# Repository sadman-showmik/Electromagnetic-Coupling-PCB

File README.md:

# Electromagnetic Coupling Link — Resonant Inductive Power Transfer

A KiCad 8 project for a **wireless power link**: a 12 V transmitter drives a tuned coil at ~75 kHz, and a galvanically isolated receiver coil picks up the field, rectifies it and regulates it to **5 V**. It uses only common through-hole parts (NE555, IR2302, IRFZ44N, LM7805).

> Full-page schematic: [`EM_Coupling/EM_Coupling.pdf`](EM_Coupling/EM_Coupling.pdf)

---

## Contents

- [How it works](#how-it-works)
- [Key design values](#key-design-values)
- [Bill of materials](#bill-of-materials)
- [Coils](#coils)
- [Expected performance](#expected-performance)
- [Repository layout](#repository-layout)
- [Opening the project](#opening-the-project)
- [Regenerating the files](#regenerating-the-files)
- [Verification](#verification)
- [Safety notes](#safety-notes)
- [Project status](#project-status)

---

## How it works

```mermaid
flowchart LR
    subgraph TX["Transmitter — 12 V side"]
        A["J1 12 V in<br/>S1 switch"] --> B["U1 NE555<br/>~75 kHz oscillator"]
        B --> C["IC1 IR2302<br/>half-bridge driver"]
        C --> D["Q1 / Q2 IRFZ44N<br/>half-bridge"]
        D --> E["C5 + TX coil<br/>series resonant tank"]
    end
    E -. "magnetic field<br/>(no wires)" .-> F
    subgraph RX["Receiver — isolated side"]
        F["RX coil + C7<br/>resonant pickup"] --> G["D3 / D4<br/>voltage doubler → C6"]
        G --> H["IC2 LM7805<br/>5 V regulator"]
        H --> I["J4 5 V out"]
        G --> J["J5 raw DC out"]
    end
```

### Transmitter (12 V)

| Stage | Parts | What it does |
|---|---|---|
| Power input | J1, S1, C8, C1 | 12 V DC in, on/off switch, input and high-frequency decoupling |
| Oscillator | U1, R1, R4, C11, C10, C2 | NE555 astable, ~75 kHz square wave, ~53 % duty |
| Gate driver | IC1, R2, C4, D2, C3 | IR2302 drives the half-bridge with built-in dead time; D2/C3 bootstrap the high-side gate |
| Power stage | Q1, Q2, R3 | IRFZ44N half-bridge switches the `SW` node between 12 V and GND |
| Resonant tank | C5, TX coil (J2) | Series LC tuned to 75 kHz — a large AC current flows in the coil and makes a strong alternating magnetic field |

### Receiver (isolated)

| Stage | Parts | What it does |
|---|---|---|
| Pickup | RX coil (J3), C7 | Coil tuned to the same 75 kHz so it captures as much energy as possible |
| Rectifier | D3, D4, C6 | Greinacher voltage doubler: about 2× the coil peak voltage as DC (`VRAW`, also on J5) |
| Regulator | IC2, C9 | LM7805 gives a steady 5 V on J4 |
| Protection | D5, D1 | D5 protects the 7805 when C6 discharges first; D1 (5.6 V zener) clamps output over-voltage |

The TX ground (`GND`) and RX ground (`GND_RX`) are **not connected**. Energy crosses only through the magnetic coupling between the two coils.

---

## Key design values

| Quantity | Formula | Value |
|---|---|---|
| Oscillator frequency | f = 1.44 / ((R1 + 2·R4) · C11) | 1.44 / ((1 k + 18.18 k) · 1 nF) ≈ **75 kHz** |
| Duty cycle | (R1 + R4) / (R1 + 2·R4) | ≈ **53 %** |
| Coil inductance for resonance | L = 1 / ((2π f)² · C) with C5 = C7 = 0.1 µF | ≈ **45 µH** per coil |
| Minimum `VRAW` for regulation | 5 V + LM7805 dropout | ≈ **7.5 V** |

---

## Bill of materials

| Reference | Value | Footprint | Qty | Notes |
|---|---|---|---|---|
| C1, C2, C3, C4, C5, C7, C9 | 0.1 µF | `Capacitor_THT:CP_Radial_Tantal_D6.0mm_P5.00mm` | 7 | **C5 and C7: use film, ≥ 250 V** (see notes below) |
| C6 | 470 µF | `Capacitor_THT:CP_Radial_Tantal_D7.0mm_P5.00mm` | 1 | Reservoir, ≥ 25 V |
| C8 | 0.33 µF | `Capacitor_THT:CP_Radial_Tantal_D7.0mm_P5.00mm` | 1 | 12 V input bypass |
| C10 | 10 nF | `Capacitor_THT:CP_Radial_Tantal_D6.0mm_P5.00mm` | 1 | 555 CV filter |
| C11 | 1 nF | `Capacitor_THT:CP_Radial_Tantal_D6.0mm_P5.00mm` | 1 | 555 timing (C0G/film recommended) |
| D1 | 1N5919BG | `3D_Models:DIOAD1405W86L465D235` | 1 | 5.6 V / 3 W zener |
| D2, D3, D4, D5 | 1N4148 | `3D_Models:DIOAD1068W53L380D172` | 4 | |
| IC1 | IR2302SPBF | `3D_Models:SOIC127P600X175-8N` | 1 | Half-bridge driver |
| IC2 | LM7805CT | `3D_Models:TO254P470X1028X1955-3P` | 1 | 5 V regulator |
| J1–J5 | 282843-2 (TE) | `3D_Models:SHDR2W130P0X1016_1X2_1524X900X1550P` | 5 | 12 V in, TX coil, RX coil, 5 V out, raw DC out |
| Q1, Q2 | IRFZ44NPBF | `3D_Models:TO254P483X1016X1994-3P` | 2 | N-MOSFET, TO-220 |
| R1 | 1 kΩ | `Resistor_THT:R_Axial_DIN0204_L3.6mm_D1.6mm_P7.62mm_Horizontal` | 1 | 555 R_A |
| R2 | 100 Ω | same | 1 | Driver input |
| R3 | 10 Ω | same | 1 | Q1 gate |
| R4 | 9.09 kΩ | same | 1 | 555 R_B |
| S1 | EG1218 | `3D_Models:EG1218` | 1 | SPDT slide switch |
| U1 | NE555P | `Package_DIP:DIP-8_W7.62mm` | 1 | Timer |

**Not in the BOM:** the two coils, about 45 µH each (see [Coils](#coils)).

> **Capacitor notes.** The BOM footprints for all capacitors are radial tantalum. That's fine for the DC parts, but **C5 and C7 carry the resonant AC current**, and the voltage across them can exceed 100 V at resonance. Fit polypropylene film capacitors rated **≥ 250 V** there; the 5 mm-pitch footprint fits most 0.1 µF film parts. The KiCad symbol for Q1/Q2 is `IRF540N` (same G-D-S TO-220 pinout), with its value set to IRFZ44NPBF.

A machine-readable BOM is in [`EM_Coupling/EM_Coupling_BOM.csv`](EM_Coupling/EM_Coupling_BOM.csv).

---

## Coils

Both coils are the same design, about **45 µH**, so they resonate at 75 kHz with 0.1 µF.

- Starting point: about **15 turns of 0.8–1.0 mm enamelled copper wire** (or Litz wire) on a **60 mm** diameter former, flat or short solenoid.
- Measure with an LCR meter and adjust turns. If your coil differs, retune: C = 1 / ((2π · 75 kHz)² · L).
- Fine-tune by trimming C5/C7, or adjust R4 to move the oscillator onto the tank's actual resonance.

---

## Expected performance

These are design estimates, not measured results.

| Parameter | Estimate |
|---|---|
| Operating frequency | ~75 kHz |
| Coupling distance | ~1–5 cm (60 mm coils, coaxial) |
| Output | 5 V regulated, roughly 0.3–0.5 W |
| Output current limit | ~100 mA (set by the 1N4148 rectifiers) |

For more output power, replace D3/D4 with faster, higher-current diodes (e.g. UF4001 or 1N5819 Schottky) and raise C6's voltage rating to suit.

---

## Repository layout

```
.
├── README.md
├── docs/
│   └── schematic.svg            # schematic image used in this README
├── EM_Coupling/                 # KiCad 8 project
│   ├── EM_Coupling.kicad_pro
│   ├── EM_Coupling.kicad_sch    # fully wired schematic
│   ├── EM_Coupling.kicad_pcb    # starter PCB: footprints and nets, not routed yet
│   ├── EM_Coupling.pdf          # printable schematic
│   ├── EM_Coupling.net          # exported netlist
│   ├── EM_Coupling_BOM.csv      # exported BOM
│   ├── erc.rpt                  # latest ERC report
│   ├── fp-lib-table             # project footprint library table
│   ├── 3D_Models.pretty/        # project-local SamacSys footprints
│   └── 3D_Models.3dshapes/      # matching STEP models
├── gen_wired.py                 # generates the wired schematic (main generator)
├── gen_schematic.py             # older label-based generator (kept as netlist reference)
├── labels_reference.net         # reference netlist used to check the wired schematic
├── kicad_lib.py                 # helper: reads KiCad symbol libraries
└── build_pcb.py                 # builds the starter PCB using KiCad's pcbnew Python
```

---

## Opening the project

1. Install **KiCad 8.0** or newer.
2. Open `EM_Coupling/EM_Coupling.kicad_pro`.
3. The project ships its own footprint library table (`fp-lib-table`). The nickname `3D_Models` resolves to `EM_Coupling/3D_Models.pretty`, so no global library setup is needed.

---

## Regenerating the files

The schematic and PCB are generated by scripts, so values and layout can be changed in code and rebuilt.

```bash
python gen_wired.py
```

```bash
"<KiCad>/bin/python.exe" build_pcb.py
```

The first command needs Python 3.9+; `kicad_lib.py` reads the symbol libraries from the KiCad install path set at the top of the file. The second must run with **KiCad's bundled Python**, because it uses the `pcbnew` module.

Run ERC and export outputs with `kicad-cli`:

```bash
kicad-cli sch erc --severity-all -o EM_Coupling/erc.rpt EM_Coupling/EM_Coupling.kicad_sch
```

```bash
kicad-cli sch export pdf -o EM_Coupling/EM_Coupling.pdf EM_Coupling/EM_Coupling.kicad_sch
```

---

## Verification

- **ERC:** 0 errors, 0 warnings (`EM_Coupling/erc.rpt`).
- **Netlist check:** the wired schematic's connectivity was compared pin-for-pin against an independently generated reference netlist (`labels_reference.net`). All 20 nets are identical.
- **Footprints:** every schematic pin maps to a footprint pad with the same number, with no missing or extra pads, for all footprints that load (see status below).
- **Not done yet:** no SPICE simulation, PCB routing or bench testing.

---

## Safety notes

- **Use a current-limited bench supply** (start at 0.5–1 A). With no receiver nearby, a series-resonant transmitter can draw a very large current and overheat the MOSFETs and coil.
- **High voltage at resonance:** C5/C7 and the coils can see over 100 V peak, even from a 12 V supply. Don't touch the tank while it's running.
- The MOSFETs and 7805 may need heatsinks at higher power.
- Keep the transmitter coil away from metal objects, which heat up in the field, and from sensitive electronics.

---

## Project status

- [x] Circuit design using the given BOM
- [x] Fully wired KiCad schematic, ERC clean
- [x] Footprints assigned per BOM; project-local footprint library with 3D models
- [x] Starter PCB with 25 of 31 footprints and their nets
- [ ] **Footprints for S1 (`EG1218`) and J1–J5 (`SHDR2W130P0X1016_1X2_1524X900X1550P`)** still need adding to `EM_Coupling/3D_Models.pretty`
- [ ] PCB placement and routing (keep the TX/RX isolation gap)
- [ ] Wind coils and tune resonance
- [ ] Bench test and measure efficiency and range

---

## Credits

- Footprints and 3D models for 1N4148, 1N5919BG, IR2302SPBF, IRFZ44NPBF and LM7805CT come from **SamacSys / Component Search Engine**. Check their terms before redistributing them in a public repository.
- Symbols and the remaining footprints are from the standard **KiCad** libraries.

## License

MIT License

Copyright (c) 2026 B M Sadman Showmi

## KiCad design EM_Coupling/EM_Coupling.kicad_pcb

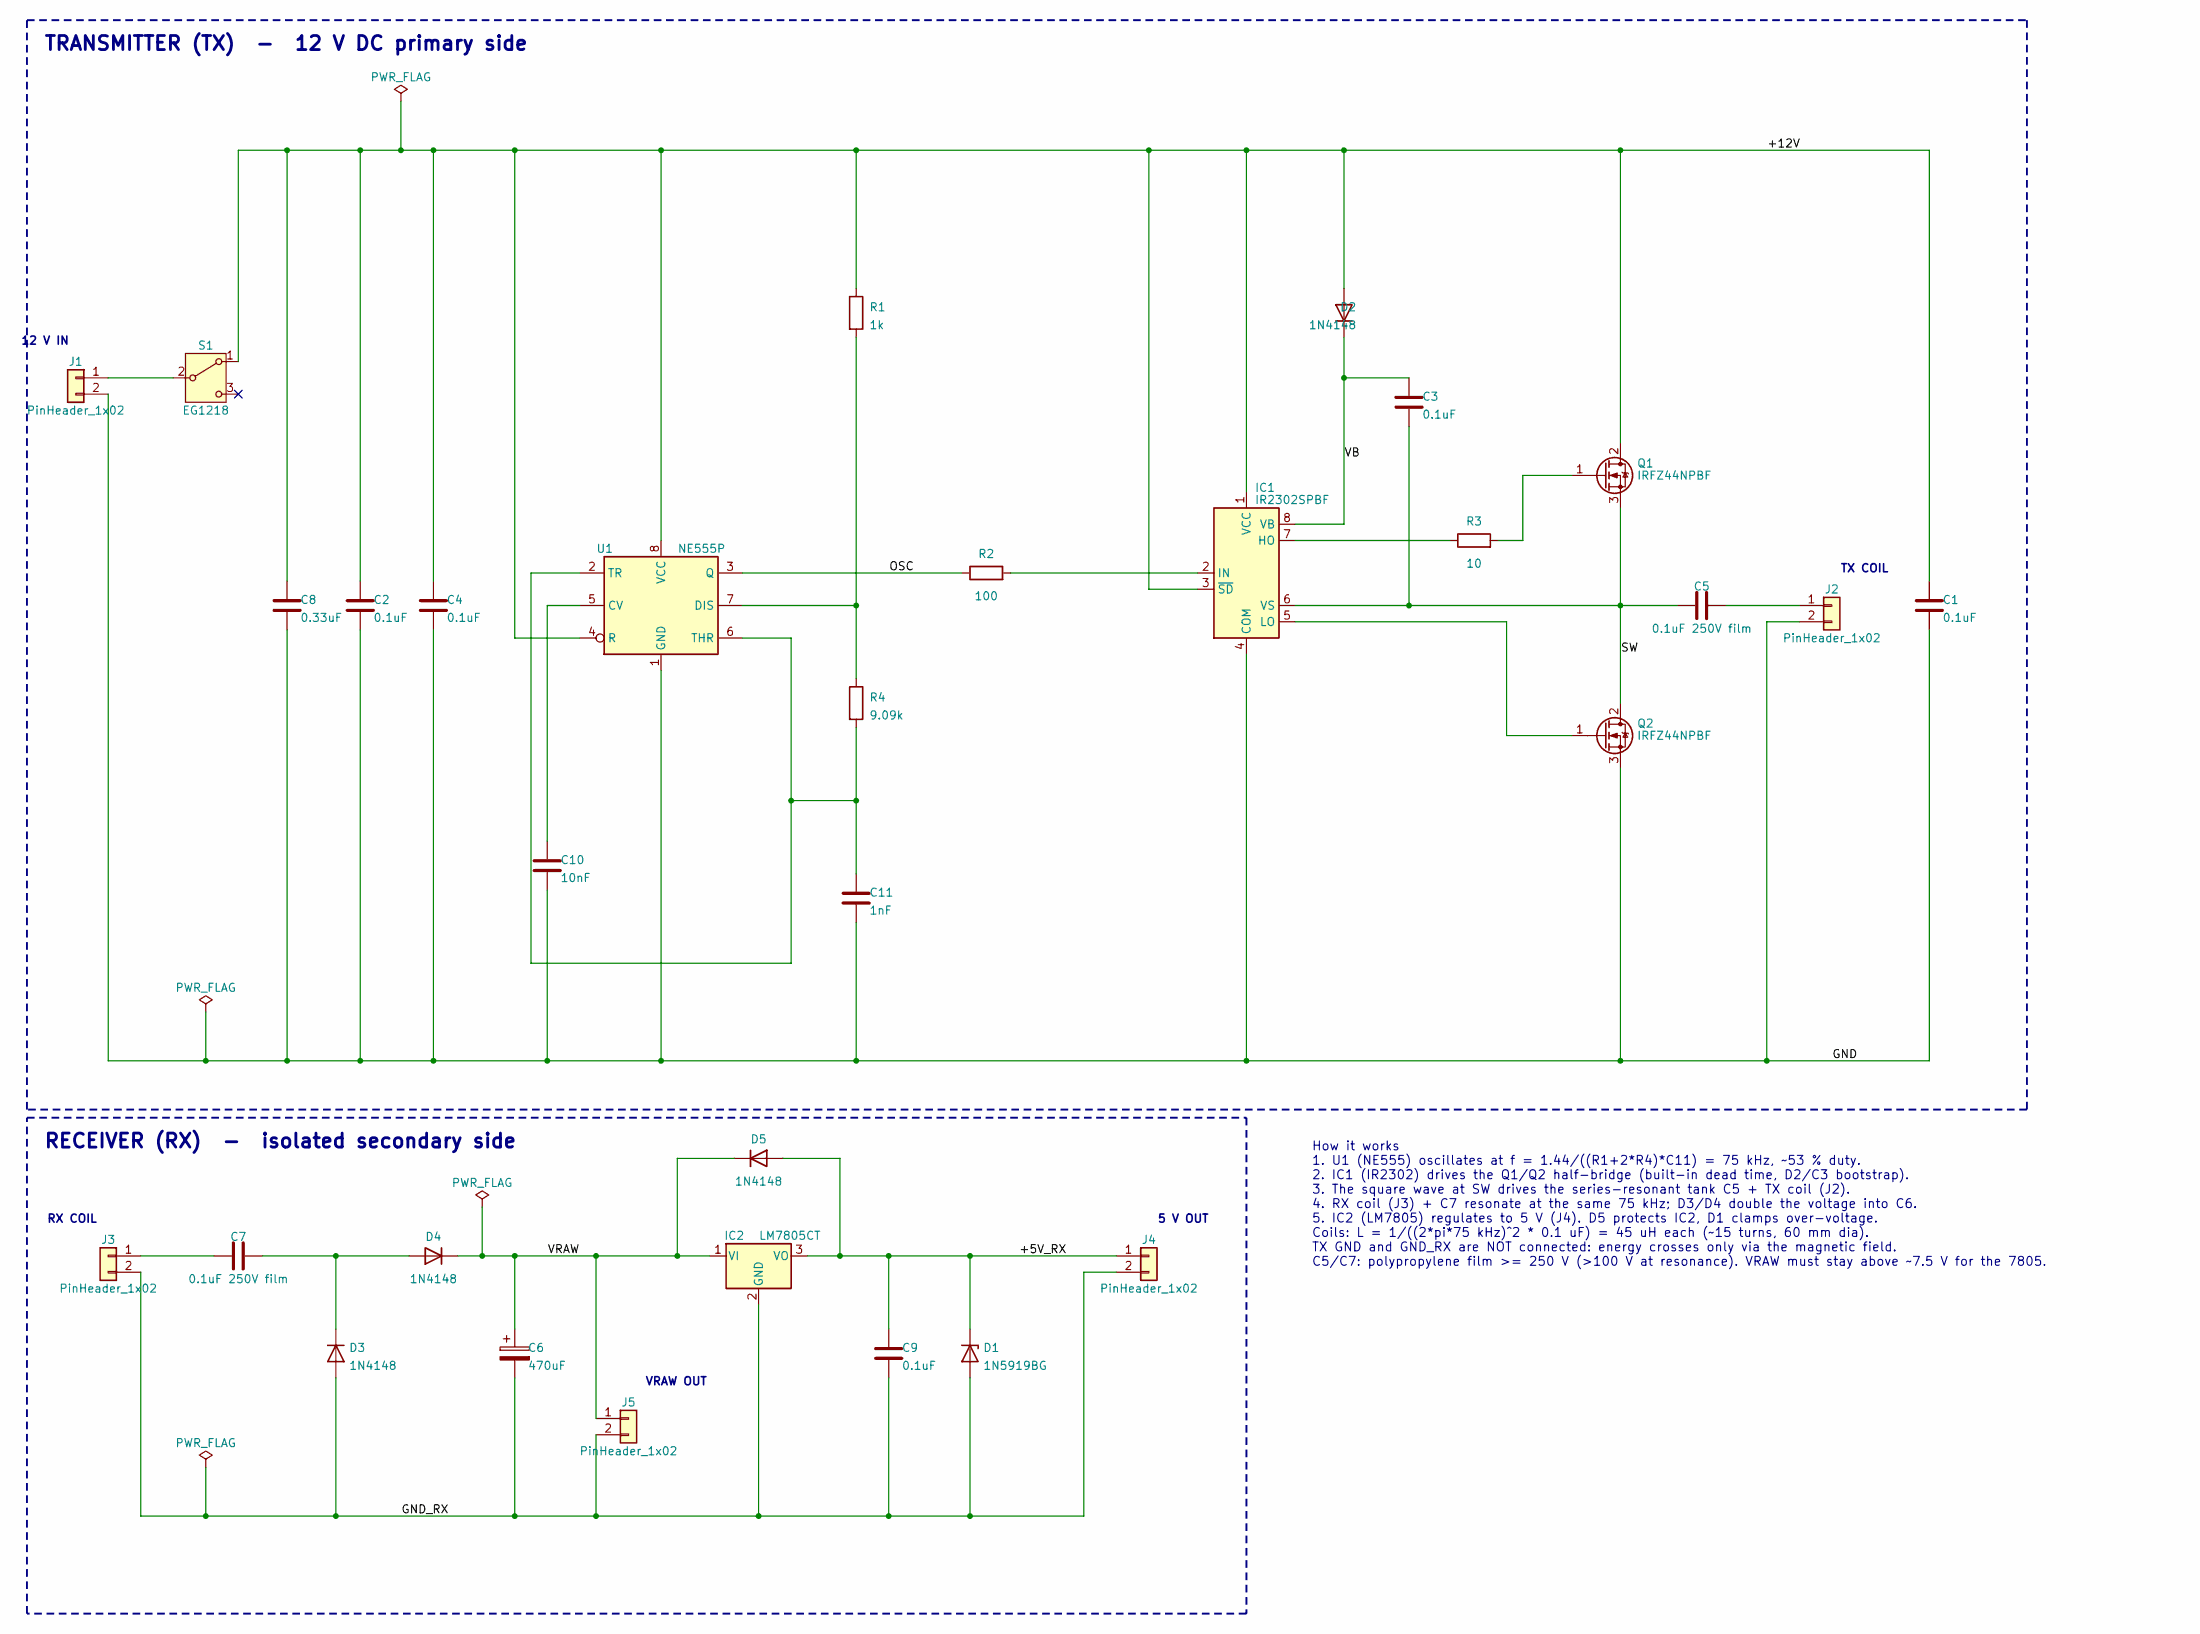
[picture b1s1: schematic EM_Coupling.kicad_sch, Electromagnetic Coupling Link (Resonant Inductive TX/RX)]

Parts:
C1, C2, C3, C4, C9: 0.1uF; CP_Radial_Tantal_D6.0mm_P5.00mm
C5, C7: 0.1uF 250V film; C_Rect_L13.0mm_W6.0mm_P10.00mm_FKS3_FKP3_MKS4
C6: 470uF; CP_Radial_Tantal_D7.0mm_P5.00mm
C8: 0.33uF; CP_Radial_Tantal_D7.0mm_P5.00mm
C10: 10nF; CP_Radial_Tantal_D6.0mm_P5.00mm
C11: 1nF; CP_Radial_Tantal_D6.0mm_P5.00mm
D1: 1N5919BG; DIOAD1405W86L465D235
D2, D3, D4, D5: 1N4148; DIOAD1068W53L380D172
IC1: IR2302SPBF; SOIC127P600X175-8N
IC2: LM7805CT; TO254P470X1028X1955-3P
J1, J2, J3, J4, J5: PinHeader_1x02; PinHeader_1x02_P2.54mm_Vertical
Q1, Q2: IRFZ44NPBF; TO254P483X1016X1994-3P
R1: 1k; R_Axial_DIN0204_L3.6mm_D1.6mm_P7.62mm_Horizontal
R2: 100; R_Axial_DIN0204_L3.6mm_D1.6mm_P7.62mm_Horizontal
R3: 10; R_Axial_DIN0204_L3.6mm_D1.6mm_P7.62mm_Horizontal
R4: 9.09k; R_Axial_DIN0204_L3.6mm_D1.6mm_P7.62mm_Horizontal
S1: EG1218; SW_SPDT_CK_JS102011SAQN
U1: NE555P; DIP-8_W7.62mm

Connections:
/+5V_RX: C9.1, D1.1 (K), D5.2 (A), IC2.3 (VO), J4.1
/+12V: C1.1, C2.1, C4.1, C8.1, D2.2 (A), IC1.1 (VCC), IC1.3 (~SD), Q1.2 (D), R1.1, S1.1 (A), U1.4 (R), U1.8 (VCC)
/GND: C1.2, C2.2, C4.2, C8.2, C10.2, C11.2, IC1.4 (COM), J1.2, J2.2, Q2.3 (S), U1.1 (GND)
/GND_RX: C6.2, C9.2, D1.2 (A), D3.2 (A), IC2.2 (GND), J3.2, J4.2, J5.2
/OSC: R2.1, U1.3 (Q)
/SW: C3.2, C5.1, IC1.6 (VS), Q1.3 (S), Q2.2 (D)
/VB: C3.1, D2.1 (K), IC1.8 (VB)
/VRAW: C6.1, D4.1 (K), D5.1 (K), IC2.1 (VI), J5.1
unnamed: C7.2, D3.1 (K), D4.2 (A)
unnamed: IC1.7 (HO), R3.1
unnamed: IC1.2 (IN), R2.2
unnamed: IC1.5 (LO), Q2.1 (G)
unnamed: J1.1, S1.2 (B)
unnamed: C5.2, J2.1
unnamed: C7.1, J3.1
unnamed: Q1.1 (G), R3.2
unnamed: C10.1, U1.5 (CV)
unnamed: R1.2, R4.1, U1.7 (DIS)
unnamed: C11.1, R4.2, U1.2 (TR), U1.6 (THR)

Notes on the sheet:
RX COIL
VRAW OUT
TRANSMITTER (TX) - 12 V DC primary side
RECEIVER (RX) - isolated secondary side
12 V IN
TX COIL
How it works 1. U1 (NE555) oscillates at f = 1.44/((R1+2*R4)*C11) = 75 kHz, ~53 % duty. 2. IC1 (IR2302) drives the Q1/Q2 half-bridge (built-in dead time, D2/C3 bootstrap). 3. The square wave at SW drives the series-resonant tank C5 + TX coil (J2). 4. RX coil (J3) + C7 resonate at the same 75 kHz; D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
5 V OUT

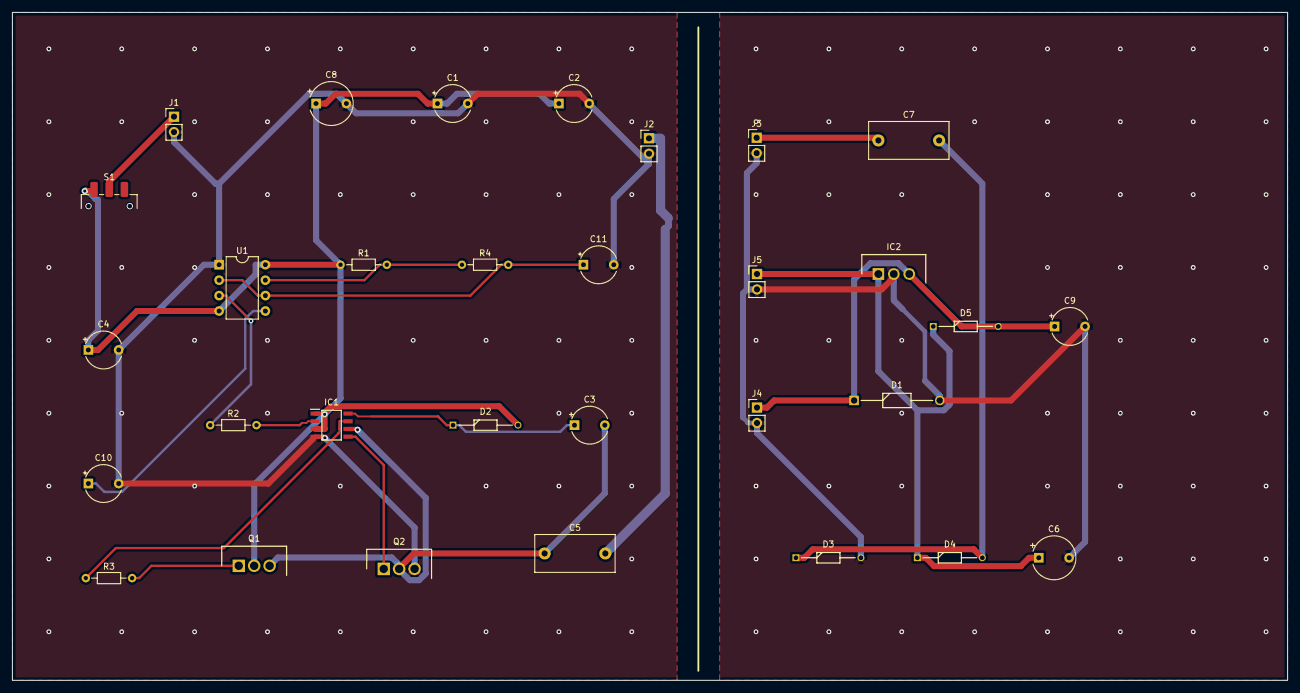
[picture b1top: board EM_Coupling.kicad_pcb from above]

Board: 2 copper layers, 210.0 x 110.0 mm, 31 parts (0 on the bottom side), 19 nets.

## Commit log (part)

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2025-11-18 Revise README for Electromagnetic Coupling PCB
    Updated the README to provide a detailed overview of the PCB project, including features, repository contents, component list, and getting started instructions.
